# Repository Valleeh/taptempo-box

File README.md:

# Tap-Tempo Box

A small foot/desk box that turns a tapped tempo into **MIDI clock** and two **switched tempo outputs** (3.5 mm TRS, opto-isolated), with an OLED display and a rotary encoder for fine adjustment. Built around an ATmega328P (Arduino Nano pinout).

## Two hardware versions

| Folder | What it is | Status |
|---|---|---|
| [`nano-perfboard/`](nano-perfboard/) | Arduino Nano + optocouplers on a 5 × 7 cm perfboard, hand-soldered. Beginner-friendly build guide. Optional variant with a second, separate TRS output (D7/D6). | Designed, layout checked |
| [`smd-pcb/`](smd-pcb/) | Custom 2-layer PCB (52 × 70 mm) assembled by JLCPCB: ATmega328P-AU, CH340C, USB-C, regulator on board. Same pin mapping, so the same firmware runs. | Designed, ERC/DRC clean, not built yet |

Both share the same 3D-printed enclosure (60 × 110 × 36 mm, CadQuery), adapted per version.

## Pin mapping (both versions)

| Function | Arduino pin |
|---|---|
| TAP button (to GND, internal pull-up) | D5 |
| Start/Stop (encoder push button) | D4 |
| Encoder A / B | D3 / D2 |
| Switched output 1 → TRS tip (PC817, 220 Ω) | D10 |
| Switched output 2 → TRS ring (PC817, 220 Ω) | D9 |
| Perfboard 2-jack variant only: output 3 → TRS 2 tip / output 4 → TRS 2 ring | D7 / D6 |
| MIDI OUT (DIN pin 5 via 220 Ω) | D1 / TX |
| OLED SDA / SCL (SSD1306, I²C) | A4 / A5 |
| Power | 9 V barrel (center negative) → Schottky → VIN |

## Repository layout

```
firmware/          Arduino sketches (currently a hardware test sketch, needs U8g2)
nano-perfboard/
  kicad/           KiCad 10 schematic + PDF
  perfboard/       perfboard layout as code (perfboard.py), drawings, build guide generator
  mech/            CadQuery enclosure, renders, collision check, STL/STEP output, 3D viewer
  share/           standalone offline HTML: build guide and 3D viewer
smd-pcb/
  kicad/           generated KiCad project (schematic, routed PCB, ERC/DRC reports)
  fab/             JLCPCB files: Gerber zip, BOM, CPL
  mech/            enclosure adapted to the SMD board
  tools/           scripts that generate the whole KiCad project and fab files
```

## Quick links

- **3D printing:** `nano-perfboard/mech/out/{tray,lid}.stl` or `smd-pcb/mech/out/{tray,lid}.stl` (print the lid top side down)
- **Build guide (perfboard, German):** open `nano-perfboard/share/taptempo-bauanleitung.html` in a browser
- **3D viewer (offline):** `nano-perfboard/share/taptempo-3d.html`
- **Ordering the SMD board:** upload the three files in `smd-pcb/fab/` to JLCPCB, details in [`smd-pcb/README.md`](smd-pcb/README.md)

## Rebuilding

Enclosure (needs CadQuery):

```sh
cd nano-perfboard/mech
python -m venv .venv && .venv/bin/pip install cadquery matplotlib
.venv/bin/python enclosure.py      # -> out/*.stl, *.step, *.glb
.venv/bin/python render.py         # -> out/view_*.png
```

Perfboard drawings and guide (plain Python 3):

```sh
cd nano-perfboard/perfboard
python3 drawings.py && python3 build_guide.py
python3 drawings.py 2trs && python3 build_guide.py 2trs   # 2-jack variant
cd ../share && python3 build_standalone.py
```

SMD board (needs KiCad 10 with its `pcbnew` Python module and `kicad-cli`):

```sh
smd-pcb/tools/build.sh
```

## Language

The detailed build documentation is in German.

## License

MIT, see [LICENSE](LICENSE).

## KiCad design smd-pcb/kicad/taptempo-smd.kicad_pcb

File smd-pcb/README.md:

# Tap-Tempo-Box – SMD-Platine für JLCPCB

Eine 2-lagige Platine (52 × 70 mm), die JLCPCB herstellt **und mit den kleinen SMD-Bauteilen bestückt**.
Der Arduino Nano ist nicht mehr aufgesteckt, seine Schaltung sitzt direkt auf der Platine:
ATmega328P-AU, USB-Chip CH340C, USB-C-Buchse und 5-V-Regler.
Die Pinbelegung ist genau wie bei der Nano-Version. Die bisherige Firmware läuft deshalb unverändert,
in der Arduino-IDE wählst du einfach **„Arduino Nano“**.

Nicht auf der Platine sind OLED, Drehgeber, TAP-Taster und MIDI-DIN-Buchse. Sie sitzen im Gehäuse und werden
mit fertigen Dupont-Kabeln an Stiftleisten gesteckt. Auf der Hinterkante der Platine sitzen USB-C,
die 9-V-Buchse und die 3,5-mm-Klinke. Sie schauen durch die Rückwand.

Stand: 25.10.2026 · ERC 0 Fehler · DRC 0 Fehler · alle Netze geroutet · Schaltplan und Platine stimmen überein.

---

## 1. Was liegt wo?

| Pfad | Inhalt |
|---|---|
| `PLAN.md` | ursprünglicher Entwurfsplan (Spezifikation) |
| `kicad/taptempo-smd.kicad_pro/.kicad_sch/.kicad_pcb` | KiCad-10-Projekt: Schaltplan und geroutete Platine mit GND-Flächen oben und unten |
| `kicad/taptempo-smd-schaltplan.pdf` | Schaltplan als PDF zum Anschauen |
| `kicad/erc.rpt`, `kicad/drc.rpt` | Prüfberichte (0 Fehler) |
| **`fab/taptempo-smd_gerber.zip`** | **für JLCPCB:** Gerber- und Bohrdaten |
| **`fab/bom_jlcpcb.csv`** | **für JLCPCB:** Stückliste (Comment, Designator, Footprint, LCSC Part #) – nur die SMD-Teile, die JLCPCB bestückt |
| **`fab/cpl_jlcpcb.csv`** | **für JLCPCB:** Bestückungsdatei (Designator, Mid X, Mid Y, Layer, Rotation), Drehwinkel schon für JLCPCB korrigiert |
| `fab/tht_selbst_loeten.csv` | Teile zum Selbst-Einlöten (Buchsen, Stiftleisten) mit LCSC-Nummern |
| `fab/vorschau_oben.png`, `fab/vorschau_unten.png`, `fab/render_3d_oben.png` | Bilder der Platine |
| `mech/enclosure.py` | angepasstes Gehäuse (CadQuery): Rückwand-Löcher an den echten Buchsen, 4 Abstandshalter an den Platinenlöchern |
| `mech/out/tray.stl/.step`, `mech/out/lid.stl/.step` | **3D-Druck-Dateien** Unterteil und Deckel |
| `mech/out/assembly.step`, `mech/out/pcb.step` | Gesamtmodell bzw. Platine als 3D-Modell |
| `mech/collide.py`, `mech/out/collision_report.txt` | Kollisionsprüfung (Ergebnis: keine Kollisionen, alle Stecker passen durch die Löcher) |
| `mech/out/view_*.png` | Ansichten Platine im Gehäuse |
| `tools/` | Skripte, die alles erzeugen (siehe Abschnitt 8) |

---

## 2. Die Schaltung in Kürze

| Funktion | Bauteil | ATmega-Pin (Arduino) |
|---|---|---|
| TAP-Taster (gegen GND, interner Pull-up) | Stecker J6 | D5 |
| Start/Stop (Taster im Drehgeber) | Stecker J5 „SW“ | D4 |
| Drehgeber A / B (je 100 nF gegen GND auf der Platine) | Stecker J5 | D3 / D2 |
| Schaltausgang 1 → Klinke **Tip** | Optokoppler U4 (220 Ω) | D10 |
| Schaltausgang 2 → Klinke **Ring** | Optokoppler U5 (220 Ω) | D9 |
| MIDI OUT: DIN-Pin 5 über 220 Ω an TX, DIN-Pin 4 über 220 Ω an +5 V, DIN-Pin 2 an GND | Stecker J7 | D1/TX |
| OLED SDA / SCL | Stecker J4 | A4 / A5 |
| Status-LED „L“ (rot) | D10 | D13 |

- **Versorgung:** 9 V über die Hohlbuchse (5,5/2,1 mm, **Minus innen** wie bei Boss-Netzteilen) →
  Verpolschutzdiode SS14 → Spannungsregler AMS1117-5.0 → +5 V.
  Alternativ USB-C: VBUS → Diode SS14 → +5 V. Die beiden Quellen speisen sich nicht gegenseitig.
  Die grüne LED zeigt an, dass Strom da ist.
- **USB:** CH340C (braucht keinen Quarz). Auto-Reset beim Hochladen über DTR → 100 nF → RESET, genau wie beim Nano.
- **Klinke:** Tip und Ring sind die Kollektoren der Optokoppler, Sleeve sind beide Emitter.
  Die Klinke ist galvanisch getrennt und **nicht** mit GND verbunden.
- **ISP-Stecker J8** (2 × 3): nur zum einmaligen Brennen des Bootloaders, siehe Abschnitt 5.

### Stecker auf der Platine (Beschriftung steht auf der Platine)

| Stecker | Pins (von Pin 1 = eckiges Pad) | Kabel zu |
|---|---|---|
| J4 OLED | 5V, SDA, SCL, GND | OLED-Modul. **Achtung:** viele Module haben die Reihenfolge GND-VCC-SCL-SDA. Kabel einzeln nach Beschriftung stecken. |
| J6 TAP | TAP, GND | TAP-Fußtaster |
| J5 DREHGEBER | A, GND, B, SW, GND | Drehgeber: A, Mitte C, B, die beiden Taster-Pins |
| J7 MIDI-DIN | 4, 2, 5 | DIN-Buchse Pin 4, Pin 2, Pin 5 (Lötseite der Buchse ansehen) |
| J8 ISP | Standard-AVR-ISP-6-Pin (1 = MISO) | USBasp oder Arduino als ISP |

---

## 3. Bauteile (BOM)

**JLCPCB bestückt 34 SMD-Teile (17 BOM-Zeilen, 138 Lötstellen)**, alle auf der Oberseite.
Alle LCSC-Nummern wurden am 25.10.2026 in der JLCPCB-Teilebibliothek geprüft (Lager, Basic/Extended, Preis).

| Teil | Designator | LCSC | Typ | Lager |
|---|---|---|---|---|
| ATmega328P-AU (TQFP-32) | U1 | C14877 | **Preferred Extended** (keine Rüstgebühr) | 42 180 |
| CH340C (SOP-16) | U2 | C84681 | **Extended** | 116 810 |
| USB-C HRO TYPE-C-31-M-12 | J1 | C165948 | **Extended** | 323 957 |
| PC817C SMD (Goodwork) | U4, U5 | C3025164 | **Extended** | 1 465 857 |
| AMS1117-5.0 (SOT-223) | U3 | C6187 | Basic | 147 984 |
| SS14 (SMA) | D1, D2 | C2480 | Basic | > 2 Mio. |
| Quarz 16 MHz 3225 (9 pF Last) | Y1 | C13738 | Basic | 192 633 |
| 12 pF C0G 0603 | C10, C11 | C38523 | Basic | 645 360 |
| 100 nF 0603 | 9 × | C14663 | Basic | 44 Mio. |
| 10 µF 25 V 0805 | C1, C16 | C15850 | Basic | 9 Mio. |
| 22 µF 0805 | C2 | C45783 | Basic | 4 Mio. |
| 220 Ω / 1 kΩ / 10 kΩ / 5,1 kΩ 0603 | R… | C22962 / C21190 / C25804 / C23186 | Basic | Millionen |
| LED grün 0805 (Power) | D3 | C2297 | Basic | 2,4 Mio. |
| LED rot 0603 („L“, D13) | D10 | C2286 | Basic | 7,8 Mio. |

→ **3 Extended-Sorten mit Rüstgebühr** (CH340C, USB-C, PC817C) und 1 Preferred-Extended-Sorte (ATmega) ohne Gebühr.
Das Ziel „≤ 5 Extended-Sorten“ ist erfüllt.

**Selbst einlöten** (Durchsteckteile, `fab/tht_selbst_loeten.csv`, 26 Lötstellen pro Platine):

| Teil | Designator | LCSC | Lager |
|---|---|---|---|
| Hohlbuchse CUI PJ-102AH (5,5/2,1 mm) | J2 | C3096093 | 1 723 |
| 3,5-mm-Stereoklinke CUI SJ1-3523N | J3 | C20182914 | 469 (eher knapp) |
| Stiftleiste 1×4 / 1×5 / 1×2 / 1×3, 2,54 mm | J4 / J5 / J6 / J7 | C2691448 / C492404 / C492401 / C2937625 | viele |
| Stiftleiste 2×3, 2,54 mm (ISP) | J8 | C65114 | 44 583 |

Die Footprints passen genau zu diesen Buchsen. Andere Hohlbuchsen oder Klinken haben meist andere Lochbilder.

---

## 4. Bestellen bei JLCPCB – Schritt für Schritt

1. Auf **jlcpcb.com** einloggen (Account anlegen machst du selbst) → **„Order now“**.
2. **„Add gerber file“** → `fab/taptempo-smd_gerber.zip` hochladen. JLCPCB erkennt 2 Lagen und 52 × 70 mm.
3. Platinen-Optionen (alles andere auf Standard lassen):
   - Base Material **FR-4**, Layers **2**, PCB Qty **5**, Thickness **1.6 mm**
   - PCB Color **Green** (billigste Farbe), Surface Finish **HASL (with lead)** oder „LeadFree HASL“
   - „Remove Order Number“: kostenlos „Yes/Specify a location“ wählen oder einfach so lassen.
     Dann druckt JLCPCB eine kleine Nummer irgendwo auf die Platine.
4. Ganz unten **„PCB Assembly“** einschalten:
   - PCBA Type **Economic**, Assembly Side **Top Side**
   - **PCBA Qty: 2** (oder 5). Du kannst 5 Platinen bestellen und nur 2 bestücken lassen. Das Minimum ist 2.
   - „Tooling holes“: **Added by JLCPCB** (das ist ok).
   - „Confirm Parts Placement“: **Yes** empfohlen (ca. 0,45 $). Dann schickt dir JLCPCB vor der Fertigung ein Foto der Bestückung zur Freigabe.
5. **„NEXT“** → Vorschau der Platine → **„NEXT“**.
6. **BOM** = `fab/bom_jlcpcb.csv` und **CPL** = `fab/cpl_jlcpcb.csv` hochladen → „Process BOM & CPL“.
7. Teileliste prüfen: Alle 17 Zeilen müssen ein Häkchen und ein gefundenes Teil haben.
   Die LCSC-Nummer steht in jeder Zeile.
   Meldet JLCPCB ein Teil als „out of stock“, nimm über „Select“ eine gleichwertige Alternative.
   Für Widerstände und Kondensatoren gilt: gleicher Wert und gleiche Größe, möglichst „Basic“.
8. **Bestückungsvorschau genau ansehen** (wichtigster Schritt, hier passieren die meisten Fehler):
   Jedes Bauteil hat einen roten Punkt für Pin 1 bzw. die Kathode. Prüfe:
   - **U1 ATmega:** der Punkt auf dem Chip muss auf der Platinenmarkierung (kleines Dreieck/„1“ an der Ecke, Richtung C13) liegen.
   - **U2 CH340C:** Pin-1-Punkt beim kleinen Dreieck neben C21.
   - **U3 AMS1117:** die breite Lasche liegt rechts (Richtung D1), die 3 schmalen Beine links.
   - **U4/U5 Optokoppler:** Punkt bei Pin 1 (Kerbe im Silkscreen-Umriss).
   - **D1, D2 (SS14):** Kathodenstrich auf der Seite der Platinenmarkierung.
   - **D3, D10 (LEDs):** Kathode wie auf der Platine markiert.
   - **J1 USB-C:** die Öffnung zeigt zur Platinenkante (nach hinten).

   Die Drehwinkel in der CPL wurden schon korrigiert: Für jedes Bauteil wurde der KiCad-Footprint mit dem
   JLCPCB-/EasyEDA-Footprint verglichen (U1 +270°, U2 +270°, U3 +180°, LEDs +180°).
   Steht trotzdem etwas verdreht da, kannst du es in der Vorschau drehen oder in `cpl_jlcpcb.csv` die Spalte „Rotation“ ändern.
9. **„NEXT“** → Preis prüfen (siehe Abschnitt 6) → „Save to cart“ → bezahlen.
   Versand: „Global Standard Direct Line“ ist am günstigsten (ca. 9–13 Tage).
   Die 19 % Mehrwertsteuer berechnet JLCPCB schon an der Kasse (IOSS), beim Zusteller zahlst du dann nichts mehr.
10. **Buchsen und Stiftleisten** gleich mitbestellen: bei **lcsc.com** die LCSC-Nummern aus
    `fab/tht_selbst_loeten.csv` in den Warenkorb legen, 5 Sätze.
    An der LCSC-Kasse kannst du laut LCSC-FAQ „Combine with JLCPCB order“ wählen, dann kommt alles in einem Paket.
    Bei JLCPCB selbst kann man Teile **nicht** einzeln mitschicken lassen.

**Selbst einlöten** (einfache Durchsteck-Lötstellen, gut für Anfänger): zuerst die Stiftleisten, dann Klinke und Hohlbuchse.
Die Teile kommen von oben in die Platine, gelötet wird unten.
Die Klinke hängt mit ihrer vorderen Nase über die Aussparung an der Platinenkante, das ist so gewollt.

---

## 5. Bootloader brennen (einmalig, JLCPCB liefert den ATmega leer)

Ohne Bootloader kann man über USB nichts hochladen. Du brauchst **einmal** einen ISP-Programmer, dafür gibt es zwei Wege.
Während des Brennens nichts anderes anschließen (kein Netzteil, kein USB an der Box).
Die Box wird über den ISP-Stecker mit 5 V versorgt.

### Weg A: zweiter Arduino (Uno/Nano) als Programmer („Arduino as ISP“)

1. In der Arduino-IDE: *Datei → Beispiele → 11.ArduinoISP → ArduinoISP* öffnen und **auf den Hilfs-Arduino** hochladen
   (Board „Arduino Uno“ bzw. „Nano“).
2. 6 Dupont-Kabel vom Hilfs-Arduino zum ISP-Stecker **J8** der Box (Pin 1 ist mit „1“ markiert, eckiges Pad):

   | Hilfs-Arduino | J8-Pin | Signal |
   |---|---|---|
   | D12 | 1 | MISO |
   | 5V | 2 | VCC |
   | D13 | 3 | SCK |
   | D11 | 4 | MOSI |
   | **D10** | 5 | RESET |
   | GND | 6 | GND |

   Beim Uno zusätzlich einen 10-µF-Elko zwischen RESET und GND des **Uno** stecken (Minus an GND),
   damit er sich nicht selbst zurücksetzt.
3. In der IDE: *Werkzeuge → Board → **Arduino Nano***, *Prozessor → **ATmega328P*** (nicht „Old Bootloader“),
   *Programmer → **Arduino as ISP***.
4. *Werkzeuge → **Bootloader brennen***. Nach ca. 10–20 s erscheint „Bootloader erfolgreich gebrannt“.
   Dabei werden auch die Fuses für den 16-MHz-Quarz gesetzt.

### Weg B: USBasp (ca. 5 € im Netz)

1. Am USBasp den Jumper auf **5 V** stellen. Das 6-polige Flachkabel direkt auf **J8** stecken
   (rote Ader bzw. Nase auf Pin 1 = „1“).
   Liegt nur ein 10-poliges Kabel bei, brauchst du einen 10→6-Adapter.
2. Arduino-IDE: Board **Arduino Nano**, Prozessor **ATmega328P**, Programmer **USBasp** → *Bootloader brennen*.
   (Unter Windows evtl. Treiber mit „Zadig“ installieren, unter Linux eine udev-Regel.)

### Danach: Firmware über USB-C hochladen

- ISP-Kabel abziehen, Box per USB-C an den Rechner. Die grüne LED leuchtet, die rote „L“-LED blinkt kurz (Bootloader).
- Board **Arduino Nano**, Prozessor **ATmega328P**, den neuen Port wählen (Linux `/dev/ttyUSB0`, Windows COMx;
  ältere Windows-Versionen brauchen evtl. den **CH340-Treiber**) → bisherigen Sketch hochladen. Fertig.

---

## 6. Kosten (Schätzung, Preise vom 25.10.2026)

Grundlage: JLCPCB-Preisseiten (PCB „ab 2 $ für 5 Stück“, grün; PCBA Economic: Einrichtung ca. 8 $,
Schablone ca. 1,50 $, 0,0016 $ pro Lötstelle, ca. 3 $ Rüstgebühr pro Extended-Sorte, Preferred Extended und Basic ohne Gebühr)
und die Teilepreise aus der JLCPCB-Bibliothek. Der Endpreis steht erst im JLCPCB-Angebot, dort bitte vergleichen.

**Echte Zahlen dieses Designs:** 34 SMD-Teile, **138 SMD-Lötstellen**, **3 Extended-Sorten mit Gebühr** (+1 Preferred),
Teilekosten ca. **3,90 $ pro Platine** (davon ATmega 2,31 $).

| Posten | 5 PCBs, **2 bestückt** | 5 PCBs, **5 bestückt** |
|---|---|---|
| Platinen (5 Stück, grün) | 2,00 $ | 2,00 $ |
| PCBA Einrichtung (Economic) | 8,00 $ | 8,00 $ |
| Schablone | 1,50 $ | 1,50 $ |
| Rüstgebühr 3 Extended-Sorten × 3 $ | 9,00 $ | 9,00 $ |
| Lötstellen 138 × 0,0016 $ pro Platine | 0,44 $ | 1,10 $ |
| Bauteile (inkl. Mindestmengen/Ausschuss, ca.) | 8,50 $ | 20,00 $ |
| „Confirm parts placement“ (optional) | 0,45 $ | 0,45 $ |
| **Zwischensumme** | **≈ 30 $** | **≈ 42 $** |
| Versand nach DE (Global Standard Direct, ca.) | ≈ 12 $ | ≈ 12 $ |
| **Summe ohne MwSt.** | **≈ 42 $** | **≈ 54 $** |
| + 19 % MwSt. (wird an der Kasse berechnet) | ≈ 8 $ | ≈ 10 $ |
| **Gesamt** | **≈ 50 $ ≈ 45 €** | **≈ 64 $ ≈ 58 €** |

Dazu kommen:
- **Buchsen + Stiftleisten** (selbst löten): ca. 2,70 $ pro Satz, 5 Sätze ≈ 14 $ zzgl. Versand von LCSC
  (zusammen mit dem JLCPCB-Paket günstiger, sonst ca. 10–20 $).
  Alternativ passende Teile aus dem eigenen Fundus: Stiftleisten sind Standard, Klinke und Hohlbuchse müssen aber genau diese Typen sein.
- Seit 1.7.2026 erhebt die EU auf Pakete unter 150 € pauschal **3 € Zoll pro Warenart**.
  Ob JLCPCB das an der Kasse mitkassiert, war nicht zu klären. Rechne mit bis zu 3–6 €.
- Optional: JLCPCB lötet auch die Durchsteckteile (3,58 $ pro Auftrag + 0,0164 $ × 26 Lötstellen pro Platine
  + vermutlich Rüstgebühren für die Buchsen). Für 2 Boxen lohnt sich das nicht. Die 26 Lötstellen schafft man selbst.
- Euro-Werte mit ca. 0,90 €/$ gerechnet, Kurs bitte prüfen.

---

## 7. Gehäuse (3D-Druck)

- `mech/out/tray.stl` (Unterteil) und `mech/out/lid.stl` (Deckel) drucken. Außenmaße 60 × 110 × 36 mm wie bisher.
- **Neu:** Rückwand-Löcher an den echten Buchsen-Positionen:

  | Buchse | x (von links, von vorne gesehen) | Höhe z | Loch |
  |---|---|---|---|
  | 9 V Hohlbuchse | 11,5 mm | 15,1 mm | Ø 10,5 mm |
  | USB-C | 28,0 mm | 10,2 mm | 13 × 7,5 mm |
  | 3,5-mm-Klinke | 46,0 mm | 11,1 mm | Ø 7 mm |

  Die Löcher sind so groß, dass die Umspritzung der Stecker durch die 2-mm-Wand passt und die Stecker ganz einrasten.
- **4 Abstandshalter** (Ø 6,5 mm, 5 mm hoch) an den Platinenlöchern bei (8 / 41,2), (52 / 41,5), (7 / 88,5), (52,5 / 88).
  Befestigung mit 4 × **M3-Blechschrauben (Kunststoffschrauben) 3 × 8 mm**, Vorbohrung 2,5 mm ist schon drin.
- Einbau-Reihenfolge: **zuerst die Platine** von oben einlegen (Buchsen an die Rückwand) und festschrauben,
  **danach die MIDI-DIN-Buchse** in die rechte Wand schrauben. Ihr Körper ragt über den rechten Platinenrand,
  mit eingebauter DIN-Buchse lässt sich die Platine nicht mehr einlegen.
  Dann die Dupont-Kabel stecken und den Deckel aufsetzen.
- Kollisionsprüfung (`mech/out/collision_report.txt`): keine Kollision zwischen Platine, Gehäuse, Drehgeber, OLED,
  TAP-Taster und DIN-Buchse. Alle drei Stecker passen durch ihre Löcher.
  Die Dupont-Stecker auf den Stiftleisten reichen bis z = 31 mm, der Deckel beginnt bei 34 mm.

---

## 8. Neu erzeugen (für später)

Alles wird aus `tools/design.py` erzeugt (Bauteile, Netze, LCSC-Nummern, Positionen):

```bash
cd tools
./build.sh            # Projekt + Schaltplan + Platine + Freerouting + GND-Flächen + ERC/DRC + fab/-Dateien
python3 jlc_rotation.py   # nur nötig, wenn Bauteile/LCSC-Nummern geändert werden (Drehwinkel für JLCPCB)
python3 lcsc_check.py C14877 "PC817"   # Teil in der JLCPCB-Bibliothek nachschlagen
cd ../mech
kicad-cli pcb export step --subst-models -f -o out/pcb.step ../kicad/taptempo-smd.kicad_pcb
../../nano-perfboard/mech/.venv/bin/python enclosure.py && ../../nano-perfboard/mech/.venv/bin/python collide.py
```

Freerouting routet bei jedem Lauf etwas anders. Nach `build.sh` immer auf „0 violations“ achten.

---

## 9. Offene Punkte / bitte prüfen

1. **Nicht in echt getestet:** Schaltplan, ERC, DRC und Mechanik sind geprüft, ein Prototyp existiert noch nicht.
   Für die erste Bestellung deshalb nur 2 Platinen bestücken lassen.
2. **Bestückungsvorschau bei JLCPCB** (Abschnitt 4, Schritt 8) gründlich prüfen. Die Drehwinkel sind berechnet, nicht praktisch erprobt.
3. **Hohlbuchse PJ-102AH:** KiCad hat kein 3D-Modell dafür.
   Die Achshöhe von 6,5 mm über der Platine ist aus dem Datenblatt geschätzt, deshalb das großzügige Ø-10,5-Loch.
   Nach dem Druck kurz anhalten, notfalls das Loch etwas aufbohren.
   Für die USB-C-Buchse gibt es ebenfalls kein Modell, sie ist als Quader nach Datenblatt modelliert.
4. **Lagerbestand der Klinke** SJ1-3523N (C20182914) ist mit 469 Stück eher knapp. Bei Bedarf vor der Bestellung nachsehen.
5. **OLED-Pinreihenfolge** am Modul prüfen (oft GND-VCC-SCL-SDA). Auf der Platine steht 5V-SDA-SCL-GND.
6. Kein Polyfuse und kein ESD-Schutz an USB. Beides wären weitere Extended-Teile mit Gebühr.
   Für ein Hobbygerät ist das unkritisch, der PC-USB-Port hat eine eigene Strombegrenzung.
7. Bei USB-Versorgung liegen nach der Diode ca. 4,6 V an statt 5 V. Das ist wie beim Original-Nano und für 16 MHz ausreichend.
8. Die EU-Zollpauschale von 3 € und der exakte JLCPCB-Endpreis sind nicht verifiziert. Siehe das Angebot an der Kasse.
9. Die Leiterbahnen hat der Autorouter verlegt. Sie sind elektrisch in Ordnung (DRC 0), aber nicht schön.
   USB D+/D− sind sehr kurz (CH340C direkt hinter der Buchse), bei 12 Mbit/s ist das unkritisch.

### Abweichungen vom PLAN.md (mit Grund)

- **Quarz-Lastkondensatoren 12 pF statt 22 pF:** Der einzige Basic-Quarz 16 MHz 3225 (C13738) ist für 9 pF Last spezifiziert.
  Daraus folgt 2 × (9 pF − ca. 3 pF Streukapazität) ≈ 12 pF.
- **SS14 für beide Dioden** (der Plan erlaubte SS14/SS34): 1 A reicht weit und spart eine BOM-Zeile.
- **Keine Polyfuse** (im Plan optional): Es gibt keine Basic-Variante, sie wäre die 4. Extended-Sorte mit Gebühr.
- **Power-LED grün in 0805** (C2297): Eine grüne 0603-LED gibt es nicht als Basic-Teil.
- **Platinengröße 52 × 70 mm** statt ideal ≤ 50 × 70: Die drei Buchsen nebeneinander brauchen die Breite.
  Das Maximum von 54 × 75 ist eingehalten, und unter 100 × 100 mm ändert sich der Preis nicht.
- **Aussparung in der Hinterkante** (7,2 × 2,2 mm) für die Klinke: Die Nase der SJ1-3523N hängt über die Kante
  und reicht 0,5 mm unter die Platinenoberfläche.
- **Abstandshalter Ø 6,5 mm für M3-Blechschrauben** (vorher M2 bei der Lochraster-Version).

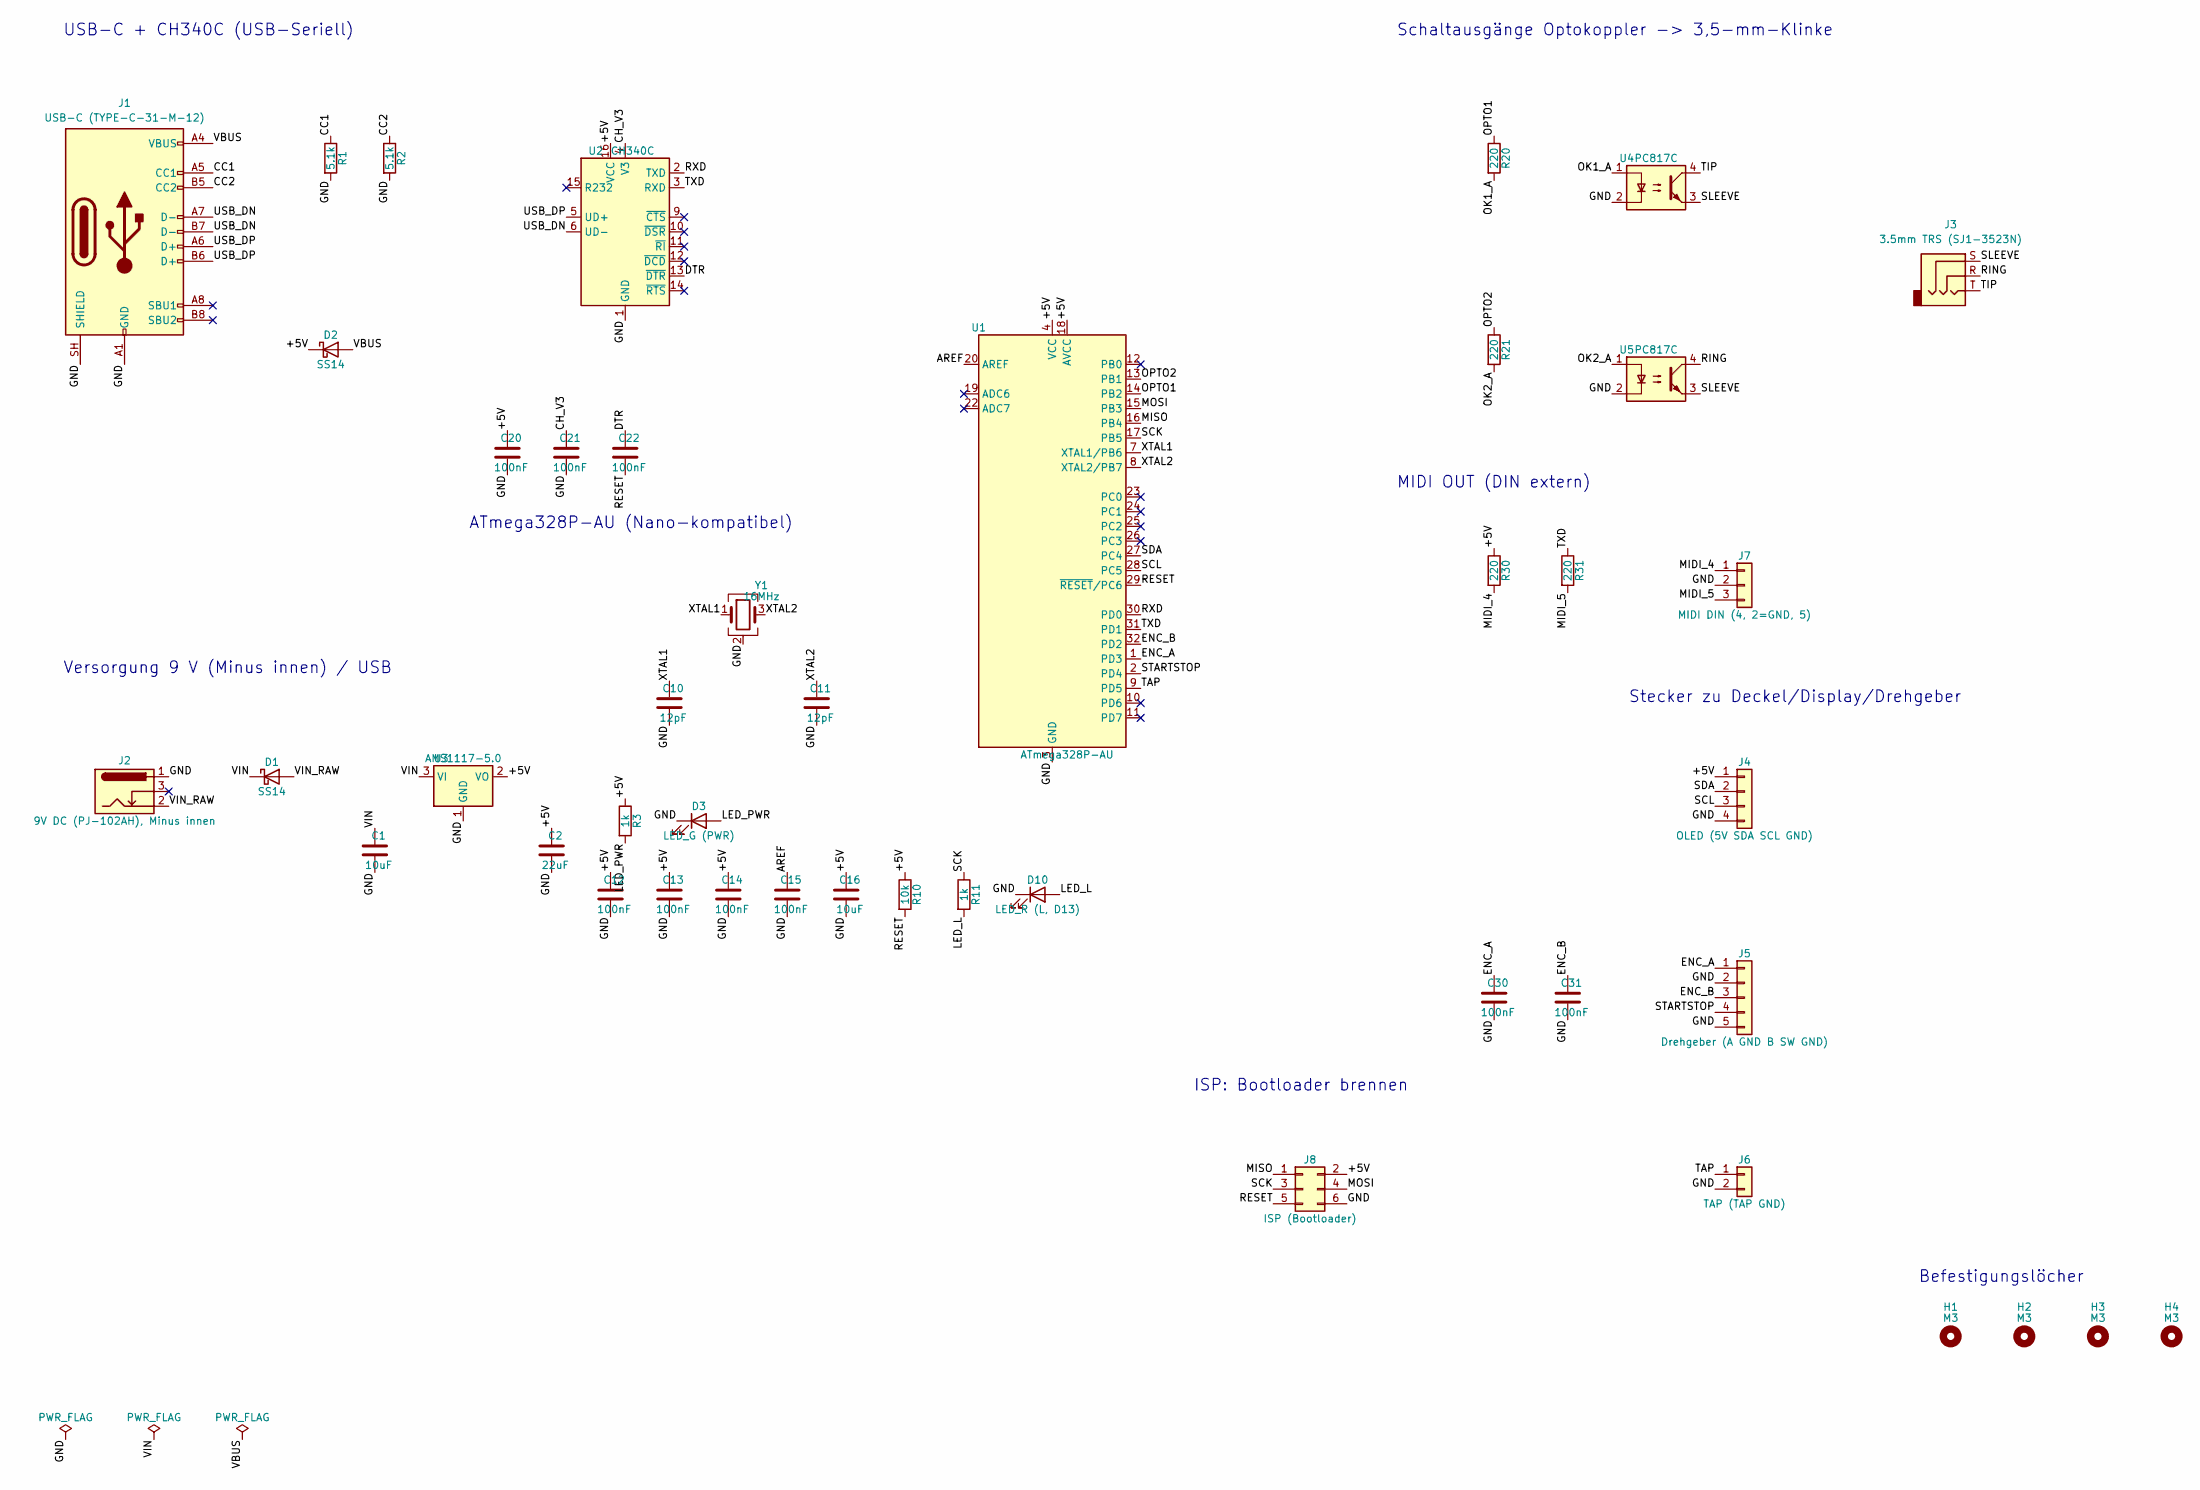
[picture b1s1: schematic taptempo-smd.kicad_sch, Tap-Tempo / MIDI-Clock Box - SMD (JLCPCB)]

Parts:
C1, C16: 10uF; C_0805_2012Metric; LCSC C15850
C2: 22uF; C_0805_2012Metric; LCSC C45783
C10, C11: 12pF; C_0603_1608Metric; LCSC C38523
C12, C13, C14, C15, C20, C21, C22, C30, C31: 100nF; C_0603_1608Metric; LCSC C14663
D1, D2: SS14; D_SMA; LCSC C2480
D3: LED_G (PWR); LED_0805_2012Metric; LCSC C2297
D10: LED_R (L, D13); LED_0603_1608Metric; LCSC C2286
H1, H2, H3, H4: M3; MountingHole_3.2mm_M3
J1: USB-C (TYPE-C-31-M-12); USB_C_Receptacle_HRO_TYPE-C-31-M-12; LCSC C165948
J2: 9V DC (PJ-102AH), Minus innen; BarrelJack_CUI_PJ-102AH_Horizontal; LCSC C3096093
J3: 3.5mm TRS (SJ1-3523N); Jack_3.5mm_CUI_SJ1-3523N_Horizontal; LCSC C20182914
J4: OLED (5V SDA SCL GND); PinHeader_1x04_P2.54mm_Vertical; LCSC C2691448
J5: Drehgeber (A GND B SW GND); PinHeader_1x05_P2.54mm_Vertical; LCSC C492404
J6: TAP (TAP GND); PinHeader_1x02_P2.54mm_Vertical; LCSC C492401
J7: MIDI DIN (4, 2=GND, 5); PinHeader_1x03_P2.54mm_Vertical; LCSC C2937625
J8: ISP (Bootloader); PinHeader_2x03_P2.54mm_Vertical; LCSC C65114
R1, R2: 5.1k; R_0603_1608Metric; LCSC C23186
R3, R11: 1k; R_0603_1608Metric; LCSC C21190
R10: 10k; R_0603_1608Metric; LCSC C25804
R20, R21, R30, R31: 220; R_0603_1608Metric; LCSC C22962
U1: ATmega328P-AU; TQFP-32_7x7mm_P0.8mm; LCSC C14877
U2: CH340C; SOIC-16_3.9x9.9mm_P1.27mm; LCSC C84681
U3: AMS1117-5.0; SOT-223-3_TabPin2; LCSC C6187
U4, U5: PC817C; SMDIP-4_W9.53mm; LCSC C3025164
Y1: 16MHz; Crystal_SMD_3225-4Pin_3.2x2.5mm; LCSC C13738

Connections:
/+5V: C2.1, C12.1, C13.1, C14.1, C16.1, C20.1, D2.1 (K), J4.1, J8.2, R3.1, R10.1, R30.1, U1.4 (VCC), U1.6 (VCC), U1.18 (AVCC), U2.16 (VCC), U3.2 (VO)
/AREF: C15.1, U1.20 (AREF)
/CC1: J1.A5 (CC1), R1.1
/CC2: J1.B5 (CC2), R2.1
/CH_V3: C21.1, U2.4 (V3)
/DTR: C22.1, U2.13 (~DTR)
/ENC_A: C30.1, J5.1, U1.1 (PD3)
/ENC_B: C31.1, J5.3, U1.32 (PD2)
/GND: C1.2, C2.2, C10.2, C11.2, C12.2, C13.2, C14.2, C15.2, C16.2, C20.2, C21.2, C30.2, C31.2, D3.1 (K), D10.1 (K), J1.A1 (GND), J1.A12 (GND), J1.B1 (GND), J1.B12 (GND), J1.SH (SHIELD), J2.1, J4.4, J5.2, J5.5, J6.2, J7.2, J8.6, R1.2, R2.2, U1.3 (GND), U1.5 (GND), U1.21 (GND), U2.1 (GND), U3.1 (GND), U4.2, U5.2, Y1.2 (G), Y1.4 (G)
/LED_L: D10.2 (A), R11.2
/LED_PWR: D3.2 (A), R3.2
/MIDI_4: J7.1, R30.2
/MIDI_5: J7.3, R31.2
/MISO: J8.1, U1.16 (PB4)
/MOSI: J8.4, U1.15 (PB3)
/OK1_A: R20.2, U4.1
/OK2_A: R21.2, U5.1
/OPTO1: R20.1, U1.14 (PB2)
/OPTO2: R21.1, U1.13 (PB1)
/RESET: C22.2, J8.5, R10.2, U1.29 (~RESET/PC6)
/RING: J3.R, U5.4
/RXD: U1.30 (PD0), U2.2 (TXD)
/SCK: J8.3, R11.1, U1.17 (PB5)
/SCL: J4.3, U1.28 (PC5)
/SDA: J4.2, U1.27 (PC4)
/SLEEVE: J3.S, U4.3, U5.3
/STARTSTOP: J5.4, U1.2 (PD4)
/TAP: J6.1, U1.9 (PD5)
/TIP: J3.T, U4.4
/TXD: R31.1, U1.31 (PD1), U2.3 (RXD)
/USB_DN: J1.A7 (D-), J1.B7 (D-), U2.6 (UD-)
/USB_DP: J1.A6 (D+), J1.B6 (D+), U2.5 (UD+)
/VBUS: D2.2 (A), J1.A4 (VBUS), J1.A9 (VBUS), J1.B4 (VBUS), J1.B9 (VBUS)
/VIN: C1.1, D1.1 (K), U3.3 (VI)
/VIN_RAW: D1.2 (A), J2.2
/XTAL1: C10.1, U1.7 (XTAL1/PB6), Y1.1
/XTAL2: C11.1, U1.8 (XTAL2/PB7), Y1.3

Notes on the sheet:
USB-C + CH340C (USB-Seriell)
Versorgung 9 V (Minus innen) / USB
ATmega328P-AU (Nano-kompatibel)
Schaltausgänge Optokoppler -> 3,5-mm-Klinke
MIDI OUT (DIN extern)
Stecker zu Deckel/Display/Drehgeber
ISP: Bootloader brennen
Befestigungslöcher

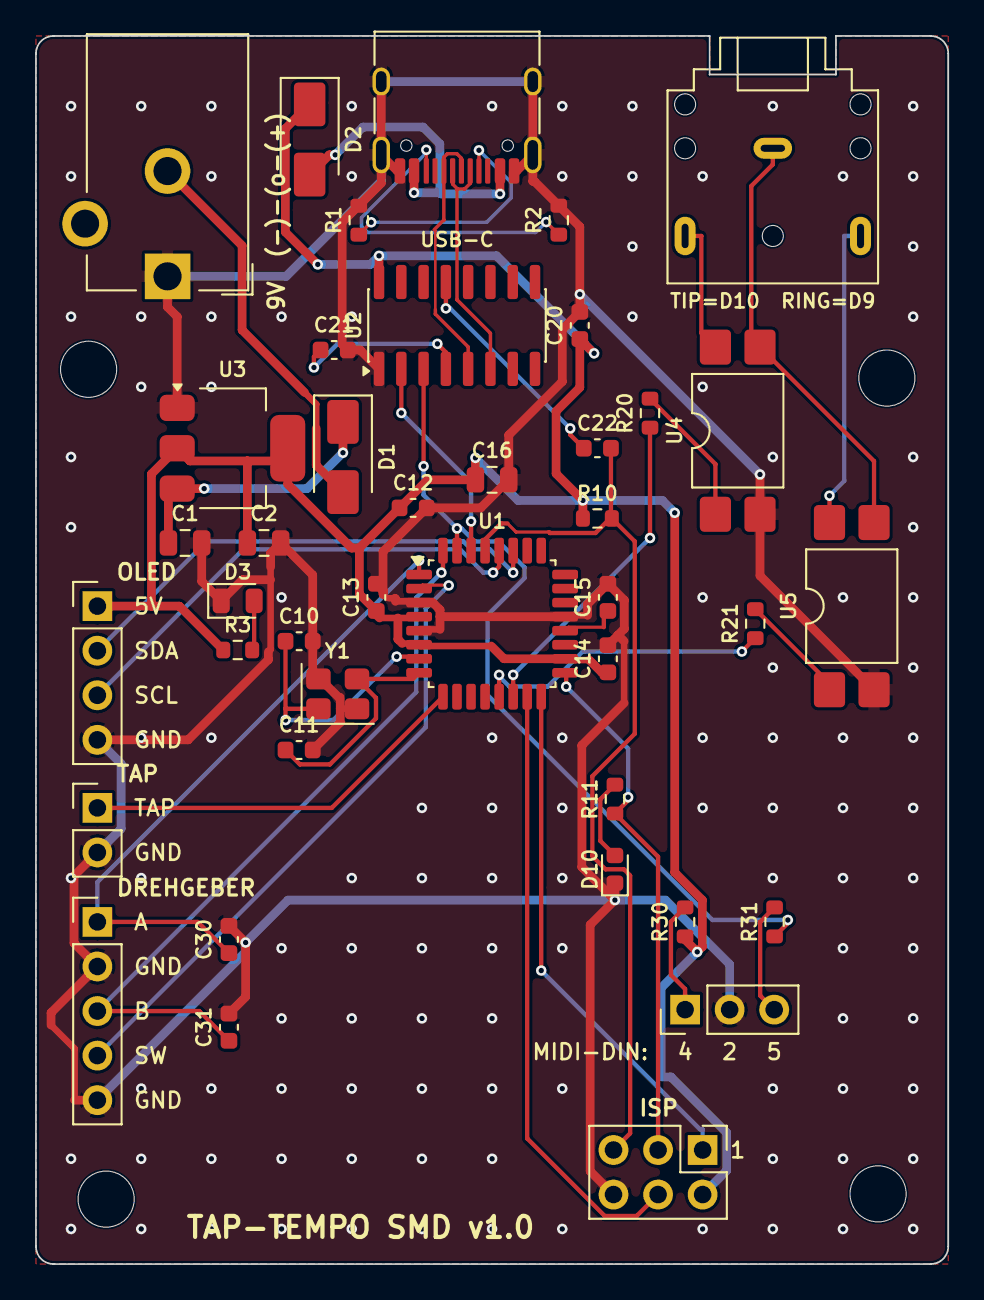
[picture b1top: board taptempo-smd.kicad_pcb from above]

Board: 2 copper layers, 52.0 x 70.0 mm, 45 parts (0 on the bottom side), 37 nets.

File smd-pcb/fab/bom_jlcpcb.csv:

Comment,Designator,Footprint,LCSC Part #
12pF,"C10,C11",C_0603_1608Metric,C38523
100nF,"C12,C13,C14,C15,C20,C21,C22,C30,C31",C_0603_1608Metric,C14663
10uF,"C1,C16",C_0805_2012Metric,C15850
22uF,C2,C_0805_2012Metric,C45783
LED_R,D10,LED_0603_1608Metric,C2286
SS14,"D1,D2",D_SMA,C2480
LED_G,D3,LED_0805_2012Metric,C2297
USB-C,J1,USB_C_Receptacle_HRO_TYPE-C-31-M-12,C165948
5.1k,"R1,R2",R_0603_1608Metric,C23186
10k,R10,R_0603_1608Metric,C25804
1k,"R3,R11",R_0603_1608Metric,C21190
220,"R20,R21,R30,R31",R_0603_1608Metric,C22962
ATmega328P-AU,U1,TQFP-32_7x7mm_P0.8mm,C14877
CH340C,U2,SOIC-16_3.9x9.9mm_P1.27mm,C84681
AMS1117-5.0,U3,SOT-223-3_TabPin2,C6187
PC817C,"U4,U5",SMDIP-4_W9.53mm,C3025164
16MHz,Y1,Crystal_SMD_3225-4Pin_3.2x2.5mm,C13738

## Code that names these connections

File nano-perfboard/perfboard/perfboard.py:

"""Perfboard (Lochraster) layout for the tap-tempo box.

Single source of truth for: connectivity check against the schematic, the
SVG build drawings and the simplified 3D model used in the enclosure.

Grid: columns A..R (18), rows 1..24 on a standard 50 x 70 mm board.
Seen from the component side, row 1 is the rear edge (USB side), column A is left.
"""
from collections import defaultdict

COLS = "ABCDEFGHIJKLMNOPQR"
ROWS = 24
PITCH = 2.54
BOARD_W, BOARD_H = 50.0, 70.0
X0 = (BOARD_W - (len(COLS) - 1) * PITCH) / 2      # board edge -> column A centre
Y0 = (BOARD_H - (ROWS - 1) * PITCH) / 2           # rear edge  -> row 1 centre
MOUNT_HOLES = [(2.5, 2.5), (BOARD_W - 2.5, 2.5), (2.5, BOARD_H - 2.5), (BOARD_W - 2.5, BOARD_H - 2.5)]


def hole_xy(h):
    """'K12' -> board-local mm (x from left edge, y from rear edge)."""
    return X0 + COLS.index(h[0]) * PITCH, Y0 + (int(h[1:]) - 1) * PITCH


def cr(h):
    return COLS.index(h[0]), int(h[1:])


def name(c, r):
    return f"{COLS[c]}{r}"


# ---------------------------------------------------------------- components
# kind decides how it is drawn / modelled; pins map hole -> (pin label, net)
NANO_LEFT = ["D13", "3V3", "REF", "A0", "A1", "A2", "A3", "A4", "A5", "A6", "A7", "5V", "RST", "GND", "VIN"]
NANO_RIGHT = ["D12", "D11", "D10", "D9", "D8", "D7", "D6", "D5", "D4", "D3", "D2", "GND", "RST", "RX0", "TX1"]
NANO_NETS = {"A4": "SDA", "A5": "SCL", "5V": "+5V", "VIN": "VIN", "D10": "OPTO1", "D9": "OPTO2",
             "D5": "TAP", "D4": "STARTSTOP", "D3": "ENC_A", "D2": "ENC_B", "TX1": "MIDI_TX"}

COMPONENTS = []


def comp(ref, kind, value, pins, **kw):
    COMPONENTS.append(dict(ref=ref, kind=kind, value=value, pins=pins, **kw))


nano_pins = {}
for i, p in enumerate(NANO_LEFT):
    nano_pins[f"E{i+1}"] = (p, "GND" if (p == "GND" and i == 13) else NANO_NETS.get(p))
for i, p in enumerate(NANO_RIGHT):
    nano_pins[f"K{i+1}"] = (p, NANO_NETS.get(p))
comp("U1", "nano", "Arduino Nano (in 2 Buchsenleisten 15-pol.)", nano_pins)

comp("R3", "res", "220 Ω", {"L3": ("1", "OPTO1"), "L7": ("2", "OK1_A")})
comp("R4", "res", "220 Ω", {"L8": ("1", "OPTO2"), "L12": ("2", "OK2_A")})
comp("U2", "dip4", "PC817 (im Sockel)", {"M7": ("1", "OK1_A"), "M8": ("2", "GND"), "P8": ("3", "SLEEVE"), "P7": ("4", "TIP")})
comp("U3", "dip4", "PC817 (im Sockel)", {"M12": ("1", "OK2_A"), "M13": ("2", "GND"), "P13": ("3", "SLEEVE"), "P12": ("4", "RING")})
comp("J7", "hdr", "Klinke (TIP, SLEEVE, RING)", {"R7": ("T", "TIP"), "R8": ("S", "SLEEVE"), "R9": ("R", "RING")})
comp("J4", "hdr", "OLED (5V, SDA, SCL, GND)", {"B7": ("5V", "+5V"), "B8": ("SDA", "SDA"), "B9": ("SCL", "SCL"), "B10": ("GND", "GND")})
comp("D1", "diode", "1N5817 (Ring zur Mitte!)", {"A20": ("A", "VIN9"), "E20": ("K", "VIN")})
comp("J3", "hdr90", "9 V (+, −)", {"A24": ("+", "VIN9"), "B24": ("−", "GND")})
comp("C1", "cap", "100 nF", {"G23": ("", "ENC_A"), "F23": ("", "GND")})
comp("C2", "cap", "100 nF", {"I23": ("", "ENC_B"), "J23": ("", "GND")})
comp("J5", "hdr90", "Drehgeber (A, C, B, SW, SW)", {"G24": ("A", "ENC_A"), "H24": ("C", "GND"), "I24": ("B", "ENC_B"),
                                                    "J24": ("SW", "STARTSTOP"), "K24": ("SW", "GND")})
comp("SW1", "hdr90", "TAP-Taster", {"M24": ("1", "TAP"), "N24": ("2", "GND")})
comp("R1", "res", "220 Ω", {"P19": ("1", "+5V"), "P23": ("2", "MIDI_4")})
comp("R2", "res", "220 Ω", {"R19": ("1", "MIDI_TX"), "R23": ("2", "MIDI_5")})
comp("J1", "hdr90", "MIDI (DIN 4, 2, 5)", {"P24": ("4", "MIDI_4"), "Q24": ("2", "GND"), "R24": ("5", "MIDI_5")})

# ---------------------------------------------------------------- wiring (solder side)
# bare: tinned wire / bent leg along a row or column, soldered at every listed point
# ins:  insulated wire between two points (may cross things)
BARE = [
    ("OPTO1", ["K3", "L3"]), ("OK1_A", ["L7", "M7"]), ("OK2_A", ["L12", "M12"]),
    ("TIP", ["P7", "R7"]), ("SLEEVE", ["P8", "R8"]), ("SLEEVE", ["Q8", "Q13"]), ("SLEEVE", ["Q13", "P13"]),
    ("SDA", ["E8", "B8"]), ("SCL", ["E9", "B9"]),
    ("GND", ["B10", "B22"]), ("GND", ["E14", "D14", "D22"]), ("GND", ["M13", "L13", "L22"]),
    ("GND", ["B22", "Q22"]),
    ("GND", ["B24", "B22"]), ("GND", ["H24", "H22"]), ("GND", ["K24", "K22"]), ("GND", ["N24", "N22"]),
    ("GND", ["Q24", "Q22"]), ("GND", ["F23", "F22"]), ("GND", ["J23", "J22"]),
    ("ENC_A", ["G23", "G24"]), ("ENC_B", ["I23", "I24"]),
    ("MIDI_4", ["P23", "P24"]), ("MIDI_5", ["R23", "R24"]),
    ("VIN9", ["A24", "A20"]), ("VIN", ["E20", "E15"]),
]
INSULATED = [
    ("OPTO2", "K4", "L8", "gelb"), ("GND", "M8", "M13", "schwarz"), ("RING", "P12", "R9", "grün"),
    ("+5V", "E12", "B7", "rot"), ("+5V", "E12", "P19", "rot"), ("MIDI_TX", "K15", "R19", "orange"),
    ("TAP", "K8", "M24", "weiß"), ("STARTSTOP", "K9", "J24", "violett"),
    ("ENC_A", "K10", "G24", "blau"), ("ENC_B", "K11", "I24", "blau"),
]

# what the schematic says (net -> pins), used for the check
EXPECTED = {
    "OPTO1": {"U1.D10", "R3.1"}, "OK1_A": {"R3.2", "U2.1"}, "OPTO2": {"U1.D9", "R4.1"}, "OK2_A": {"R4.2", "U3.1"},
    "TIP": {"U2.4", "J7.T"}, "SLEEVE": {"U2.3", "U3.3", "J7.S"}, "RING": {"U3.4", "J7.R"},
    "SDA": {"U1.A4", "J4.SDA"}, "SCL": {"U1.A5", "J4.SCL"}, "+5V": {"U1.5V", "J4.5V", "R1.1"},
    "MIDI_4": {"R1.2", "J1.4"}, "MIDI_TX": {"U1.TX1", "R2.1"}, "MIDI_5": {"R2.2", "J1.5"},
    "TAP": {"U1.D5", "SW1.1"}, "STARTSTOP": {"U1.D4", "J5.SW@J24"}, "ENC_A": {"U1.D3", "J5.A", "C1.ENC_A"},
    "ENC_B": {"U1.D2", "J5.B", "C2.ENC_B"}, "VIN9": {"J3.+", "D1.A"}, "VIN": {"D1.K", "U1.VIN"},
    "GND": {"U1.GND@E14", "U2.2", "U3.2", "J4.GND", "J3.−", "J5.C", "J5.SW@K24", "C1.GND", "C2.GND", "SW1.2", "J1.2"},
}


def pin_id(c, hole, label, net):
    if c["kind"] == "cap":
        return f"{c['ref']}.{net}"
    if c["ref"] == "J5" and label == "SW" or c["ref"] == "U1" and label == "GND":
        return f"{c['ref']}.{label}@{hole}"
    return f"{c['ref']}.{label}"


def check(components=None, bare=None, insulated=None, expected=None):
    """Verify the layout against the schematic. Defaults to this module's data;
    variants (e.g. perfboard_2trs.py) pass their own lists."""
    components = COMPONENTS if components is None else components
    bare = BARE if bare is None else bare
    insulated = INSULATED if insulated is None else insulated
    expected = EXPECTED if expected is None else expected
    errors = []
    pin_at = {}
    for c in components:
        for h, (label, net) in c["pins"].items():
            if h in pin_at:
                errors.append(f"hole {h} used twice ({pin_at[h][0]} and {c['ref']})")
            pin_at[h] = (c["ref"], pin_id(c, h, label, net), net)
            col, row = cr(h)
            assert 0 <= col < len(COLS) and 1 <= row <= ROWS, h

    parent = {}
    def find(a):
        parent.setdefault(a, a)
        while parent[a] != a:
            parent[a] = parent[parent[a]]; a = parent[a]
        return a
    def union(a, b): parent[find(a)] = find(b)

    bare_owner = {}
    for net, pts in bare:
        for a, b in zip(pts, pts[1:]):
            (ca, ra), (cb, rb) = cr(a), cr(b)
            if ca != cb and ra != rb:
                errors.append(f"bare wire {a}-{b} not straight")
                continue
            steps = max(abs(cb - ca), abs(rb - ra))
            for k in range(steps + 1):
                h = name(ca + (cb - ca) * k // steps, ra + (rb - ra) * k // steps)
                if h in pin_at and pin_at[h][2] != net:
                    errors.append(f"bare wire {net} {a}-{b} touches {h} ({pin_at[h][1]}, net {pin_at[h][2]})")
                if h in bare_owner and bare_owner[h] != net:
                    errors.append(f"bare wires {bare_owner[h]} and {net} share hole {h}")
                bare_owner[h] = net
                union(h, a)
    for net, a, b, _ in insulated:
        for h in (a, b):
            if h not in pin_at and h not in bare_owner:
                errors.append(f"insulated wire {net} ends at empty hole {h}")
        union(a, b)

    groups = defaultdict(set)
    for h, (ref, pid, net) in pin_at.items():
        groups[find(h)].add(pid)
    found = {frozenset(g) for g in groups.values() if len(g) > 1}
    want = {frozenset(v) for v in expected.values()}
    for g in want - found:
        errors.append("net incomplete or merged: " + ", ".join(sorted(g)))
    for g in found - want:
        errors.append("unexpected connection: " + ", ".join(sorted(g)))
    return errors


if __name__ == "__main__":
    errs = check()
    print("\n".join(errs) if errs else f"OK: {len(EXPECTED)} Netze stimmen mit dem Schaltplan überein, "
          f"{len(BARE)} blanke Brücken, {len(INSULATED)} isolierte Drähte")
